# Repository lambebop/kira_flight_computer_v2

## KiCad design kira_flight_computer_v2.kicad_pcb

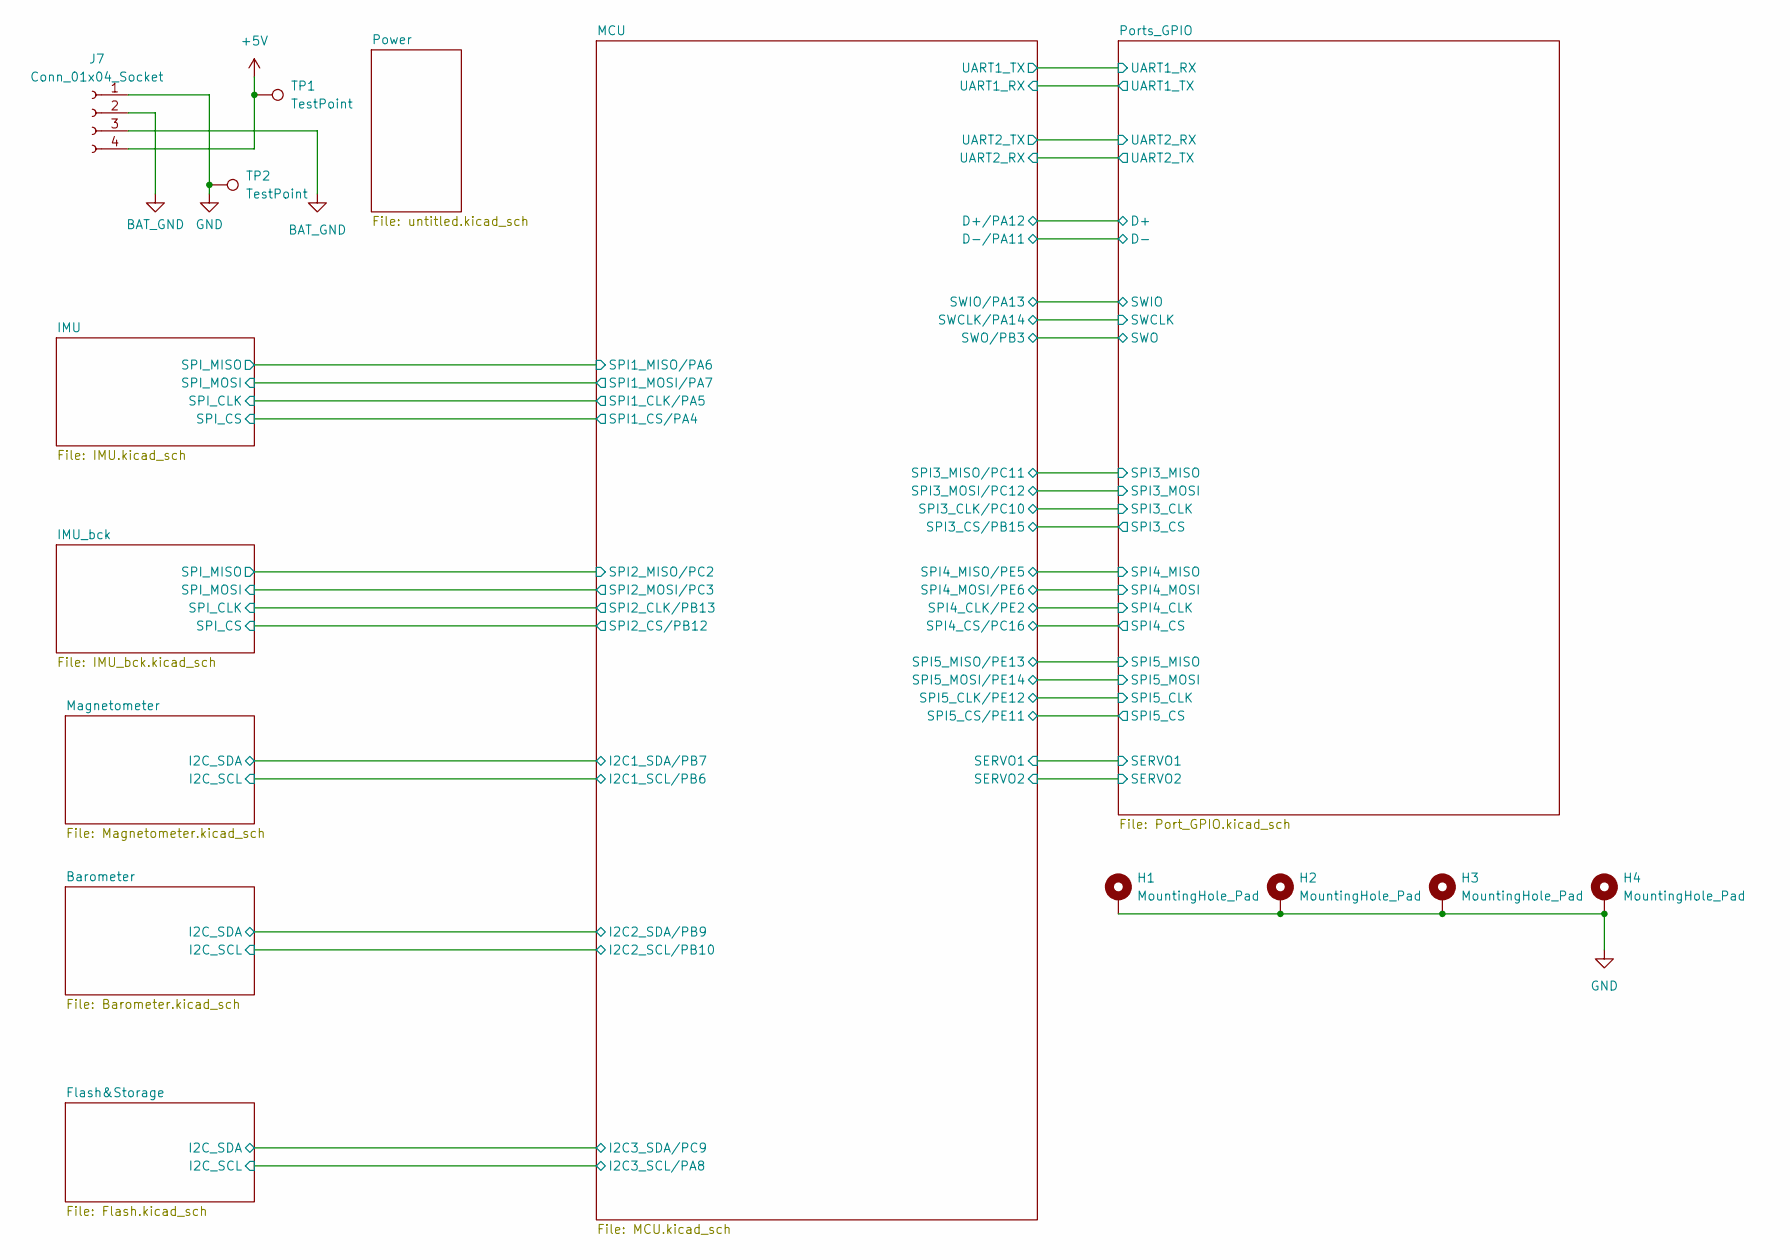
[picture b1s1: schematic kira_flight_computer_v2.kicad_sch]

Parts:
H1, H2, H3, H4: MountingHole_Pad; MountingHole_2.2mm_M2_Pad_TopBottom
J7: Conn_01x04_Socket; TerminalBlock_WAGO_2601-1104_1x04_P3.50mm_Horizontal
TP1, TP2: TestPoint; TestPoint_Pad_D1.0mm

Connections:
+5V: J7.4, TP1.1; also elsewhere on the board
BAT_GND: J7.2, J7.3
GND: H1.1, H2.1, H3.1, H4.1, J7.1, TP2.1; also elsewhere on the board

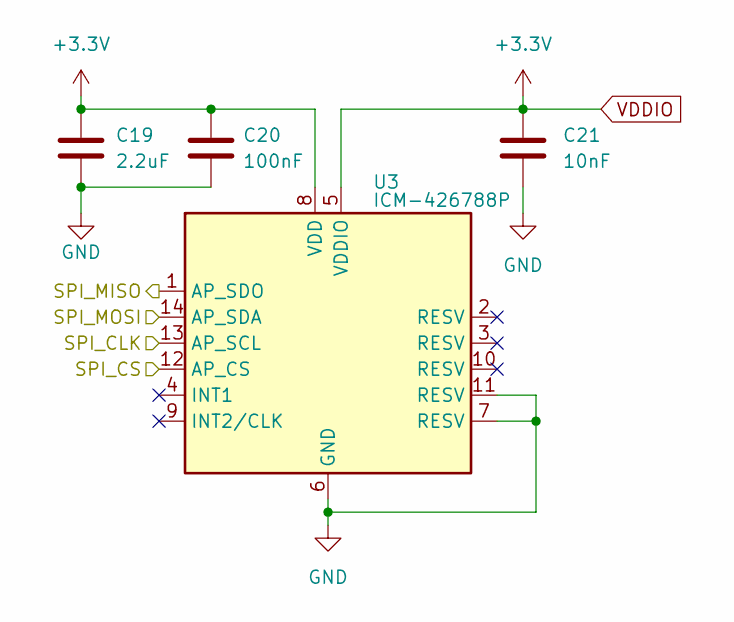
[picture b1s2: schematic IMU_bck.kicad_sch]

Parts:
C19: 2.2uF; C_0603_1608Metric_Pad1.08x0.95mm_HandSolder
C20: 100nF; C_0603_1608Metric_Pad1.08x0.95mm_HandSolder
C21: 10nF; C_0603_1608Metric_Pad1.08x0.95mm_HandSolder
U3: ICM-426788P; Bosch_LGA-14_3x2.5mm_P0.5mm

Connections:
/IMU_bck/SPI_CLK: U3.13 (AP_SCL); also elsewhere on the board
/IMU_bck/SPI_CS: U3.12 (AP_CS); also elsewhere on the board
/IMU_bck/SPI_MISO: U3.1 (AP_SDO); also elsewhere on the board
/IMU_bck/SPI_MOSI: U3.14 (AP_SDA); also elsewhere on the board
GND: C19.2, C20.2, C21.2, U3.6 (GND), U3.7 (RESV), U3.11 (RESV); also elsewhere on the board
VDDIO: C19.1, C20.1, C21.1, U3.5 (VDDIO), U3.8 (VDD); also elsewhere on the board

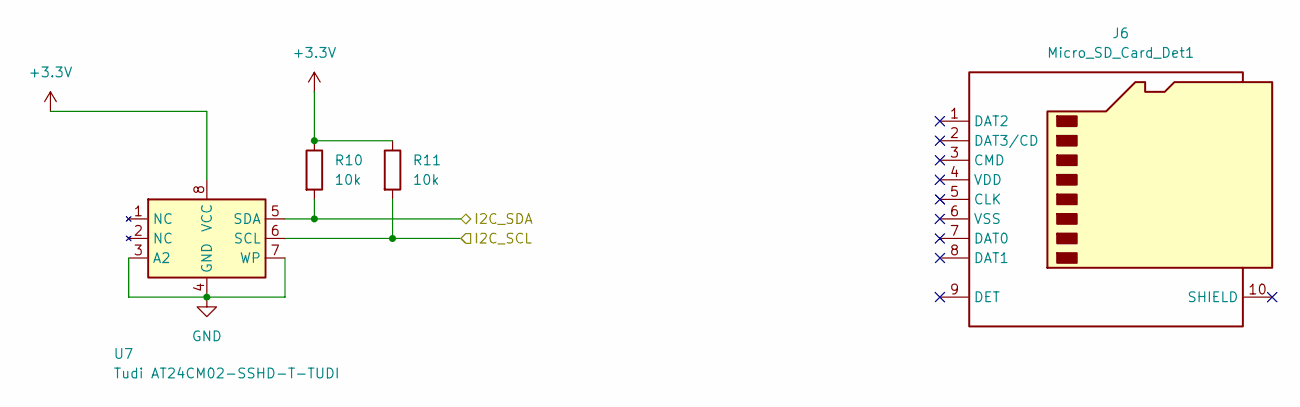
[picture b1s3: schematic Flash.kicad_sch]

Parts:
J6: Micro_SD_Card_Det1
R10, R11: 10k; R_0603_1608Metric
U7: Tudi AT24CM02-SSHD-T-TUDI; SOIC-8_3.9x4.9mm_P1.27mm

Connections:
/Flash&Storage/I2C_SCL: R11.2, U7.6 (SCL); also elsewhere on the board
/Flash&Storage/I2C_SDA: R10.2, U7.5 (SDA); also elsewhere on the board
GND: U7.3 (A2), U7.4 (GND), U7.7 (WP); also elsewhere on the board
VDDIO: R10.1, R11.1, U7.8 (VCC); also elsewhere on the board

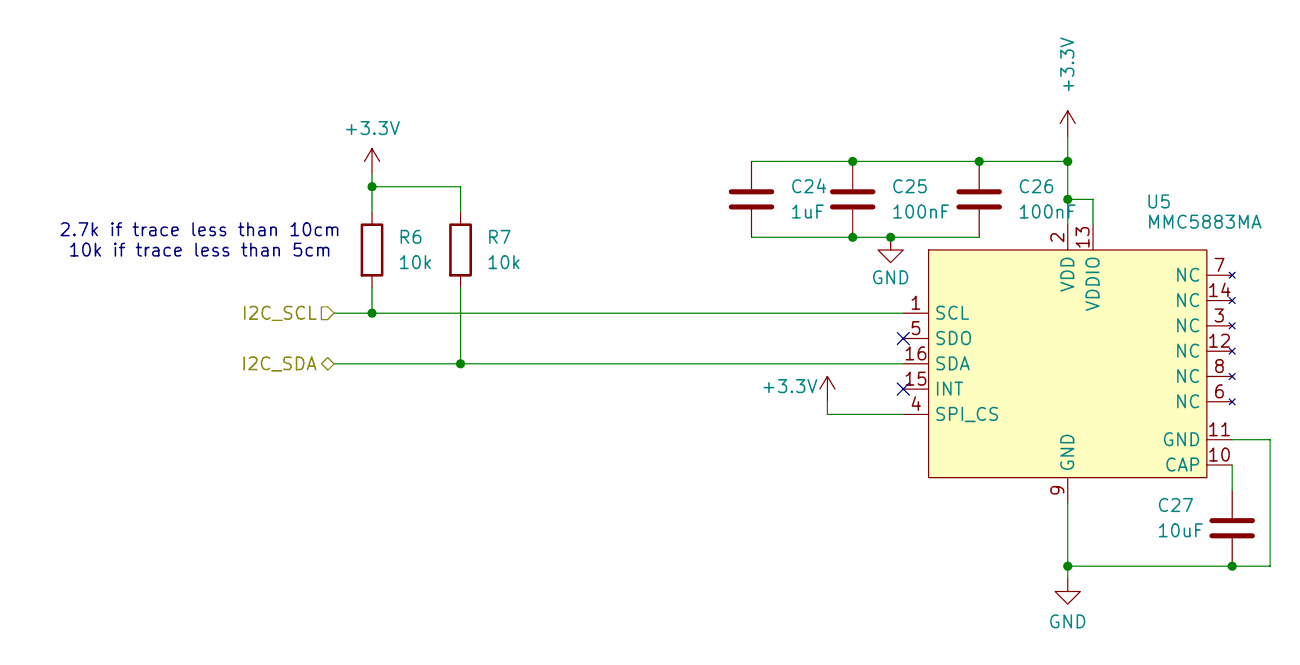
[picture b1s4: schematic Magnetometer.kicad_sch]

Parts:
C24: 1uF; C_0603_1608Metric_Pad1.08x0.95mm_HandSolder
C25, C26: 100nF; C_0603_1608Metric_Pad1.08x0.95mm_HandSolder
C27: 10uF; C_0603_1608Metric_Pad1.08x0.95mm_HandSolder
R6, R7: 10k; R_0603_1608Metric_Pad0.98x0.95mm_HandSolder
U5: MMC5883MA; LGA-16_3x3mm_P0.5mm

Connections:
/MCU/I2C1_SCL/PB6: R6.2, U5.1 (SCL); also elsewhere on the board
/MCU/I2C1_SDA/PB7: R7.2, U5.16 (SDA); also elsewhere on the board
GND: C24.2, C25.2, C26.2, C27.2, U5.9 (GND), U5.11 (GND); also elsewhere on the board
unnamed: C27.1, U5.10 (CAP)
VDDIO: C24.1, C25.1, C26.1, R6.1, R7.1, U5.2 (VDD), U5.4 (SPI_CS), U5.13 (VDDIO); also elsewhere on the board

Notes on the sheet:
2.7k if trace less than 10cm 10k if trace less than 5cm

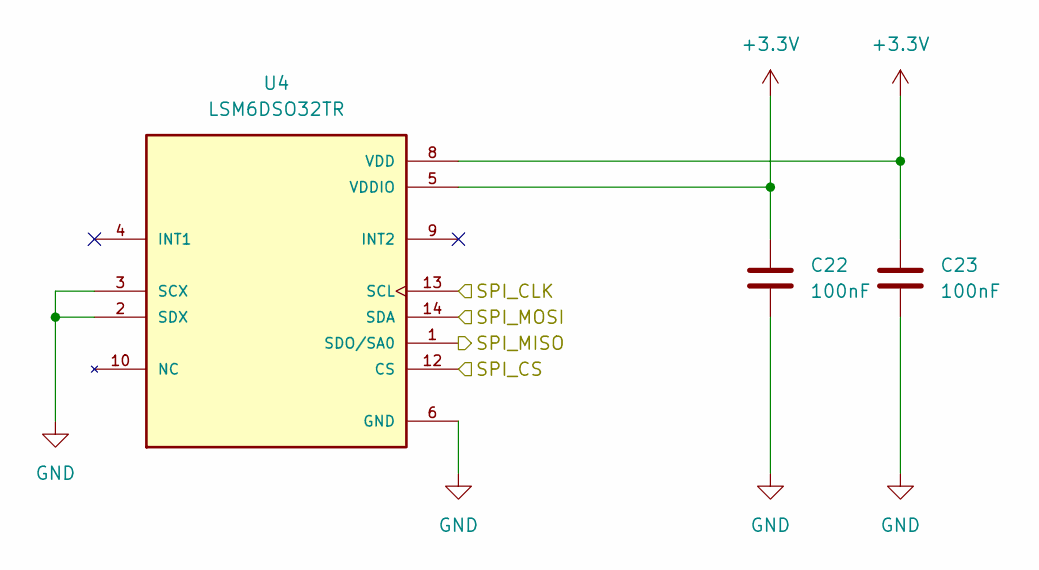
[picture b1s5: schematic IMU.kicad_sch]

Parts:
C22, C23: 100nF; C_0603_1608Metric_Pad1.08x0.95mm_HandSolder
U4: LSM6DSO32TR; XDCR_LSM6DSO32TR; PARTREV 1

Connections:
/IMU/SPI_CLK: U4.13 (SCL); also elsewhere on the board
/IMU/SPI_CS: U4.12 (CS); also elsewhere on the board
/IMU/SPI_MISO: U4.1 (SDO/SA0); also elsewhere on the board
/IMU/SPI_MOSI: U4.14 (SDA); also elsewhere on the board
GND: C22.2, C23.2, U4.2 (SDX), U4.3 (SCX), U4.6 (GND), U4.7 (GND); also elsewhere on the board
VDDIO: C22.1, C23.1, U4.5 (VDDIO), U4.8 (VDD); also elsewhere on the board

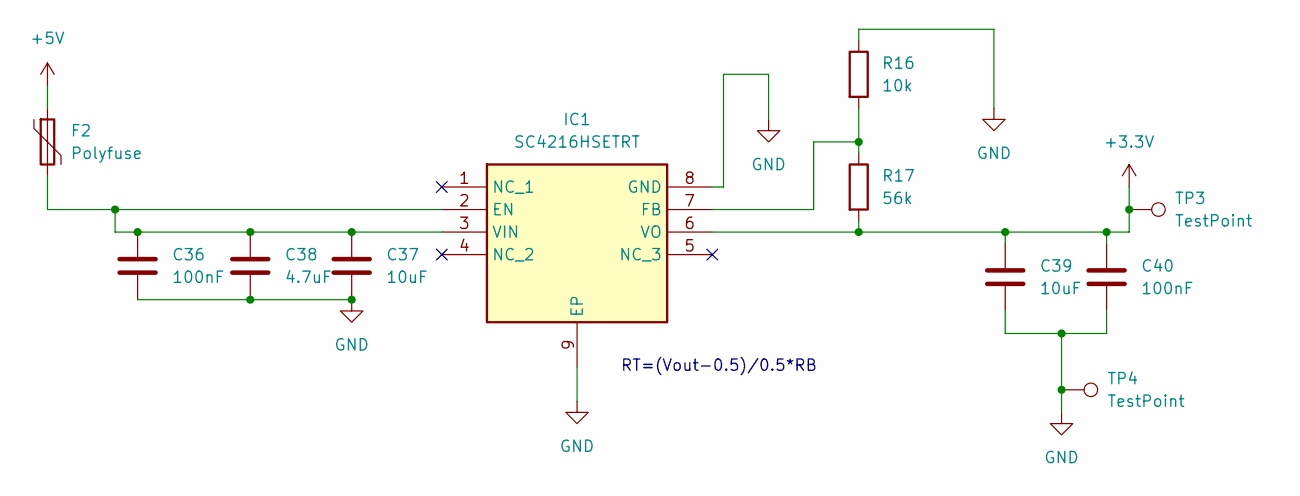
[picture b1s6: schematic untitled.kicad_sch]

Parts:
C36, C40: 100nF; C_0603_1608Metric
C37, C39: 10uF; C_1206_3216Metric
C38: 4.7uF; C_0603_1608Metric
F2: Polyfuse; Fuse_1206_3216Metric_Pad1.42x1.75mm_HandSolder
IC1: SC4216HSETRT; SOIC127P600X175-9N; Mouser Part Number 947-SC4216HSETRT
R16: 10k; R_0603_1608Metric
R17: 56k; R_0805_2012Metric
TP3, TP4: TestPoint; TestPoint_Pad_D1.0mm

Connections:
+5V: F2.1; also elsewhere on the board
GND: C36.2, C37.2, C38.2, C39.2, C40.2, IC1.8 (GND), IC1.9 (EP), R16.1, TP4.1; also elsewhere on the board
unnamed: C36.1, C37.1, C38.1, F2.2, IC1.2 (EN), IC1.3 (VIN)
unnamed: IC1.7 (FB), R16.2, R17.1
VDDIO: C39.1, C40.1, IC1.6 (VO), R17.2, TP3.1; also elsewhere on the board

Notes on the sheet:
RT=(Vout-0.5)/0.5*RB

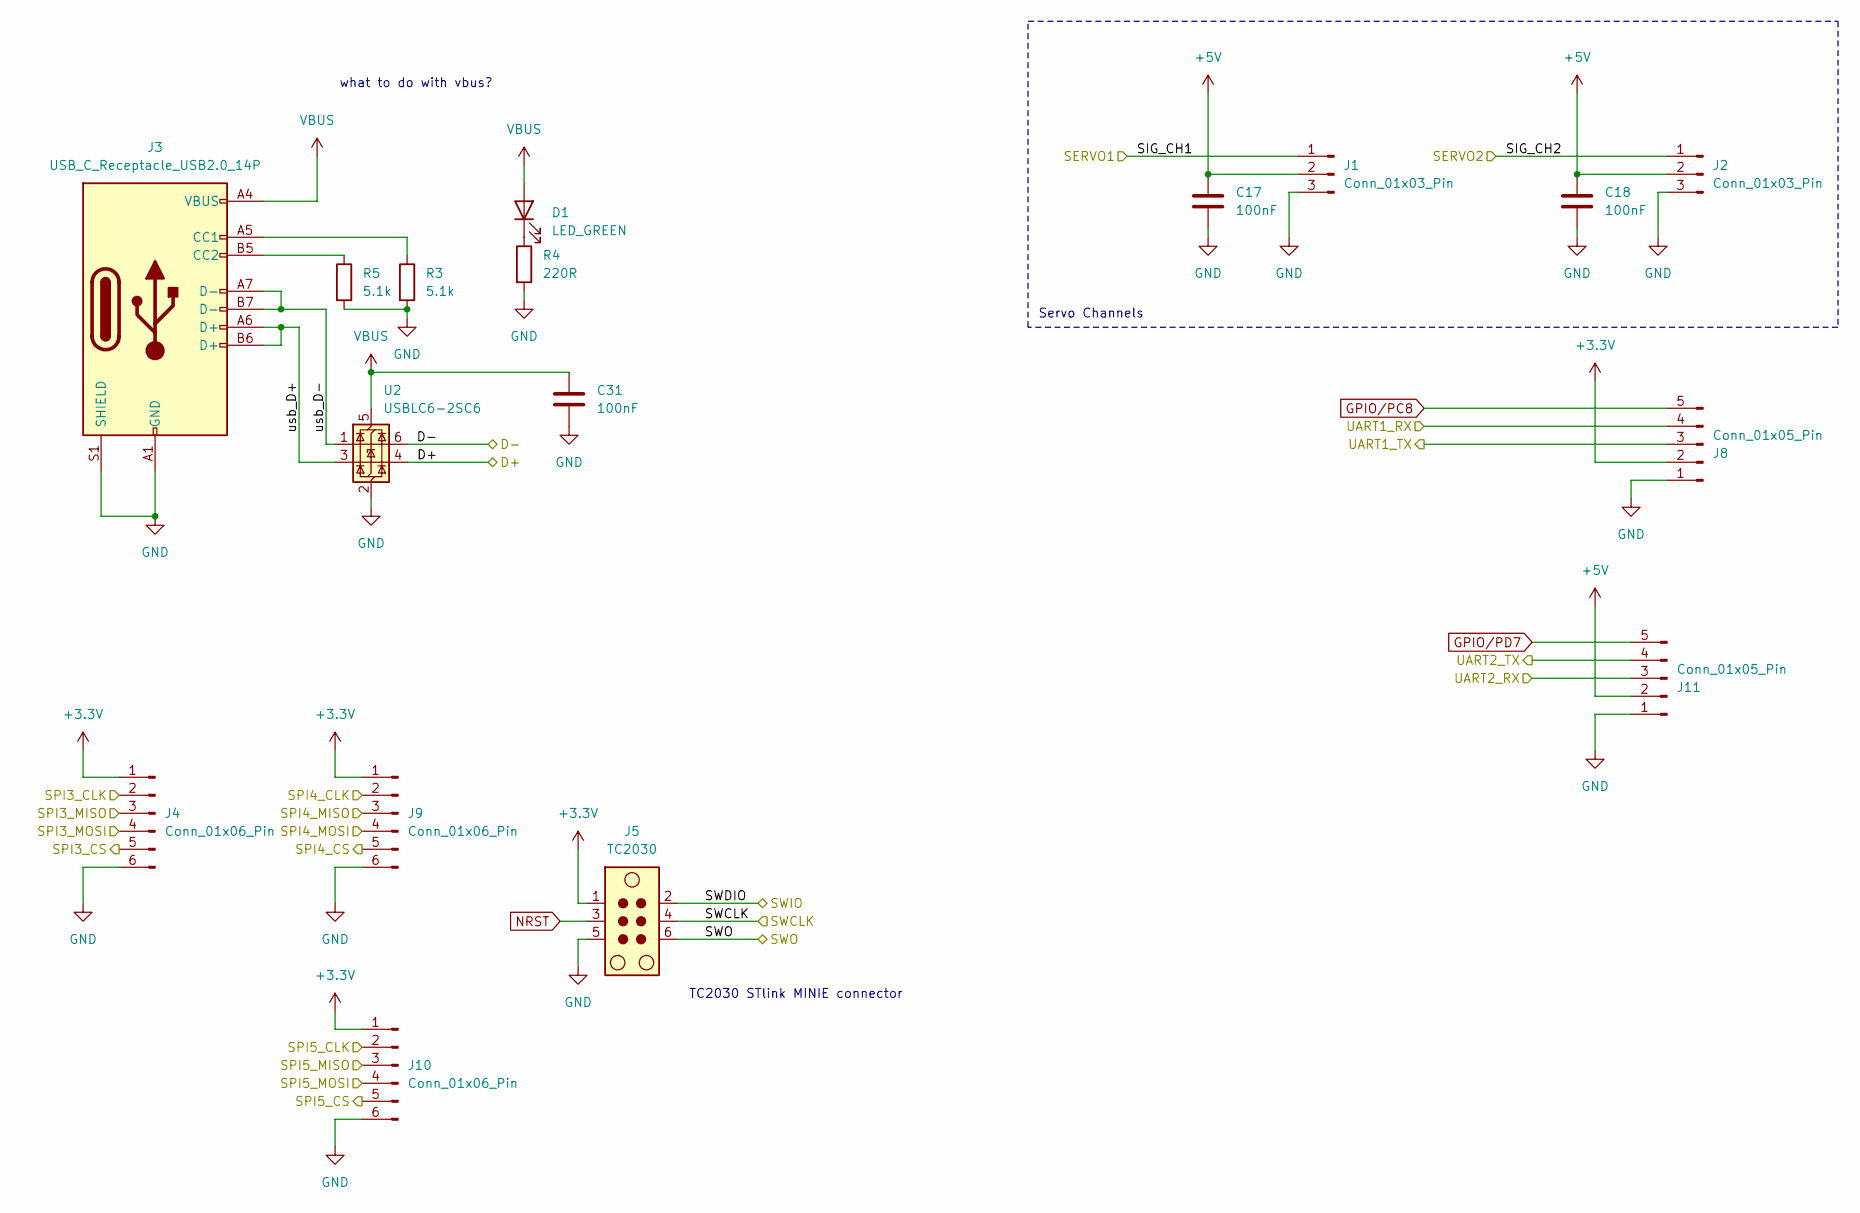
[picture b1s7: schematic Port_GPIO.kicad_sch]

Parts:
C17, C18, C31: 100nF; C_0603_1608Metric_Pad1.08x0.95mm_HandSolder
D1: LED_GREEN; LED_0603_1608Metric
J1, J2: Conn_01x03_Pin; JST_XH_S3B-XH-A_1x03_P2.50mm_Horizontal
J3: USB_C_Receptacle_USB2.0_14P; USB_C_Receptacle_GCT_USB4105-xx-A_16P_TopMnt_Horizontal
J4, J9, J10: Conn_01x06_Pin; JST_GH_BM06B-GHS-TBT_1x06-1MP_P1.25mm_Vertical
J5: TC2030; Tag-Connect_TC2030-IDC-NL_2x03_P1.27mm_Vertical
J8, J11: Conn_01x05_Pin; JST_GH_BM05B-GHS-TBT_1x05-1MP_P1.25mm_Vertical
R3, R5: 5.1k; R_0603_1608Metric_Pad0.98x0.95mm_HandSolder
R4: 220R; R_0603_1608Metric_Pad0.98x0.95mm_HandSolder
U2: USBLC6-2SC6; SOT-23-6

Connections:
+5V: C17.1, C18.1, J1.2, J2.2, J11.2; also elsewhere on the board
/MCU/SPI3_CLK/PC10: J4.2; also elsewhere on the board
/MCU/SPI3_CS/PB15: J4.5; also elsewhere on the board
/MCU/SPI3_MISO/PC11: J4.3; also elsewhere on the board
/MCU/SPI3_MOSI/PC12: J4.4; also elsewhere on the board
/MCU/SPI4_CLK/PE2: J9.2; also elsewhere on the board
/MCU/SPI4_CS/PC16: J9.5; also elsewhere on the board
/MCU/SPI4_MISO/PE5: J9.3; also elsewhere on the board
/MCU/SPI4_MOSI/PE6: J9.4; also elsewhere on the board
/MCU/SPI5_CLK/PE12: J10.2; also elsewhere on the board
/MCU/SPI5_CS/PE11: J10.5; also elsewhere on the board
/MCU/SPI5_MISO/PE13: J10.3; also elsewhere on the board
/MCU/SPI5_MOSI/PE14: J10.4; also elsewhere on the board
/MCU/UART1_RX: J8.3; also elsewhere on the board
/MCU/UART1_TX: J8.4; also elsewhere on the board
/MCU/UART2_RX: J11.4; also elsewhere on the board
/MCU/UART2_TX: J11.3; also elsewhere on the board
/Ports_GPIO/D+: U2.4 (I/O2); also elsewhere on the board
/Ports_GPIO/D-: U2.6 (I/O1); also elsewhere on the board
/Ports_GPIO/SIG_CH1: J1.1; also elsewhere on the board
/Ports_GPIO/SIG_CH2: J2.1; also elsewhere on the board
/Ports_GPIO/SWCLK: J5.4; also elsewhere on the board
/Ports_GPIO/SWDIO: J5.2; also elsewhere on the board
/Ports_GPIO/SWO: J5.6; also elsewhere on the board
/Ports_GPIO/usb_D+: J3.A6 (D+), J3.B6 (D+), U2.3 (I/O2)
/Ports_GPIO/usb_D-: J3.A7 (D-), J3.B7 (D-), U2.1 (I/O1)
GND: C17.2, C18.2, C31.2, J1.3, J2.3, J3.A1 (GND), J3.A12 (GND), J3.B1 (GND), J3.B12 (GND), J3.S1 (SHIELD), J4.6, J5.5, J8.1, J9.6, J10.6, J11.1, R3.2, R4.2, R5.2, U2.2 (GND); also elsewhere on the board
GPIO/PC8: J8.5; also elsewhere on the board
GPIO/PD7: J11.5; also elsewhere on the board
NRST: J5.3; also elsewhere on the board
unnamed: D1.1 (K), R4.1
unnamed: J3.A5 (CC1), R3.1
unnamed: J3.B5 (CC2), R5.1
VBUS: C31.1, D1.2 (A), J3.A4 (VBUS), J3.A9 (VBUS), J3.B4 (VBUS), J3.B9 (VBUS), U2.5 (VBUS)
VDDIO: J4.1, J5.1, J8.2, J9.1, J10.1; also elsewhere on the board

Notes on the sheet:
what to do with vbus?
TC2030 STlink MINIE connector
Servo Channels

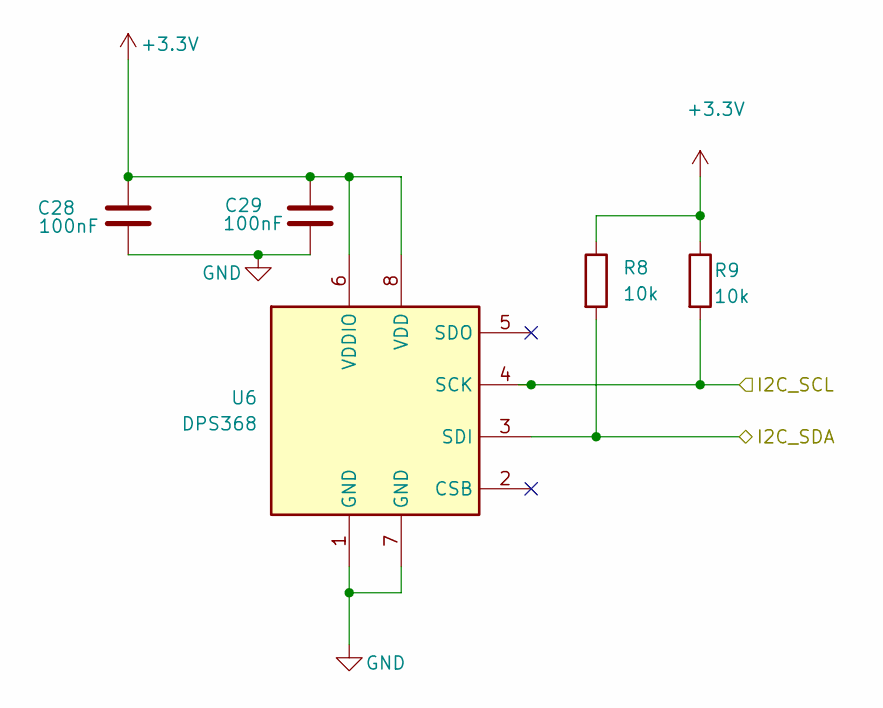
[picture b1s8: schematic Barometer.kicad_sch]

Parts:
C28, C29: 100nF; C_0603_1608Metric_Pad1.08x0.95mm_HandSolder
R8, R9: 10k; R_0603_1608Metric
U6: DPS368; Bosch_LGA-8_2x2.5mm_P0.65mm_ClockwisePinNumbering

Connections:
/Barometer/I2C_SCL: R9.2, U6.4 (SCK); also elsewhere on the board
/Barometer/I2C_SDA: R8.2, U6.3 (SDI); also elsewhere on the board
GND: C28.2, C29.2, U6.1 (GND), U6.7 (GND); also elsewhere on the board
VDDIO: C28.1, C29.1, R8.1, R9.1, U6.6 (VDDIO), U6.8 (VDD); also elsewhere on the board

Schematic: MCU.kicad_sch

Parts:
C1, C2, C30: 100nF; C_0603_1608Metric
C3, C4, C5, C6, C7, C9, C12, C14: 100nF; C_0603_1608Metric_Pad1.08x0.95mm_HandSolder
C8: 4.7uF; C_0603_1608Metric
C10, C13: 1uF; C_0603_1608Metric_Pad1.08x0.95mm_HandSolder
C11, C15, C16: 4.7uF; C_0603_1608Metric_Pad1.08x0.95mm_HandSolder
FB1: 120R; L_1206_3216Metric
R1, R2: 10k; R_0603_1608Metric
SW1: SW_SPST; SW_SPST_B3U-1000P-B
U1: STM32F411VETx; LQFP-100_14x14mm_P0.5mm
U8: USBLC6-2SC6; SOT-23-6
Y1: Resonator; Crystal_SMD_SeikoEpson_TSX3225-4Pin_3.2x2.5mm

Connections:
+5V: C30.1, U8.5 (VBUS); also elsewhere on the board
/Barometer/I2C_SCL: U1.47 (PB10); also elsewhere on the board
/Barometer/I2C_SDA: U1.96 (PB9); also elsewhere on the board
/Flash&Storage/I2C_SCL: U1.67 (PA8); also elsewhere on the board
/Flash&Storage/I2C_SDA: U1.66 (PC9); also elsewhere on the board
/IMU/SPI_CLK: U1.30 (PA5); also elsewhere on the board
/IMU/SPI_CS: U1.29 (PA4); also elsewhere on the board
/IMU/SPI_MISO: U1.31 (PA6); also elsewhere on the board
/IMU/SPI_MOSI: U1.32 (PA7); also elsewhere on the board
/IMU_bck/SPI_CLK: U1.52 (PB13); also elsewhere on the board
/IMU_bck/SPI_CS: U1.51 (PB12); also elsewhere on the board
/IMU_bck/SPI_MISO: U1.17 (PC2); also elsewhere on the board
/IMU_bck/SPI_MOSI: U1.18 (PC3); also elsewhere on the board
/MCU/I2C1_SCL/PB6: U1.92 (PB6); also elsewhere on the board
/MCU/I2C1_SDA/PB7: U1.93 (PB7); also elsewhere on the board
/MCU/SPI3_CLK/PC10: U1.78 (PC10); also elsewhere on the board
/MCU/SPI3_CS/PB15: U1.54 (PB15); also elsewhere on the board
/MCU/SPI3_MISO/PC11: U1.79 (PC11); also elsewhere on the board
/MCU/SPI3_MOSI/PC12: U1.80 (PC12); also elsewhere on the board
/MCU/SPI4_CLK/PE2: U1.1 (PE2); also elsewhere on the board
/MCU/SPI4_CS/PC16: U1.16 (PC1); also elsewhere on the board
/MCU/SPI4_MISO/PE5: U1.4 (PE5); also elsewhere on the board
/MCU/SPI4_MOSI/PE6: U1.5 (PE6); also elsewhere on the board
/MCU/SPI5_CLK/PE12: U1.43 (PE12); also elsewhere on the board
/MCU/SPI5_CS/PE11: U1.42 (PE11); also elsewhere on the board
/MCU/SPI5_MISO/PE13: U1.44 (PE13); also elsewhere on the board
/MCU/SPI5_MOSI/PE14: U1.45 (PE14); also elsewhere on the board
/MCU/UART1_RX: U1.69 (PA10); also elsewhere on the board
/MCU/UART1_TX: U1.68 (PA9); also elsewhere on the board
/MCU/UART2_RX: U1.87 (PD6); also elsewhere on the board
/MCU/UART2_TX: U1.86 (PD5); also elsewhere on the board
/Ports_GPIO/D+: U1.71 (PA12); also elsewhere on the board
/Ports_GPIO/D-: U1.70 (PA11); also elsewhere on the board
/Ports_GPIO/SIG_CH1: U8.4 (I/O2); also elsewhere on the board
/Ports_GPIO/SIG_CH2: U8.6 (I/O1); also elsewhere on the board
/Ports_GPIO/SWCLK: U1.76 (PA14); also elsewhere on the board
/Ports_GPIO/SWDIO: U1.72 (PA13); also elsewhere on the board
/Ports_GPIO/SWO: U1.89 (PB3); also elsewhere on the board
GND: C1.2, C2.2, C3.2, C4.2, C5.2, C6.2, C7.2, C8.2, C9.2, C10.2, C11.2, C12.2, C13.2, C14.2, C15.2, C16.2, C30.2, R2.1, U1.10 (VSS), U1.20 (VSSA), U1.27 (VSS), U1.49 (VSS), U1.74 (VSS), U1.99 (VSS), U8.2 (GND), Y1.2; also elsewhere on the board
GPIO/PC8: U1.65 (PC8); also elsewhere on the board
GPIO/PD7: U1.88 (PD7); also elsewhere on the board
NRST: C14.1, R1.1, U1.14 (NRST); also elsewhere on the board
unnamed: R2.2, SW1.2 (B), U1.94 (BOOT0)
unnamed: U1.90 (PB4), U8.3 (I/O2)
unnamed: U1.91 (PB5), U8.1 (I/O1)
unnamed: U1.12 (PH0), Y1.1
unnamed: U1.13 (PH1), Y1.3
unnamed: C15.1, U1.48 (VCAP1)
unnamed: C16.1, U1.73 (VCAP2)
VDDIO: C1.1, C2.1, C3.1, C4.1, C5.1, C6.1, C7.1, C8.1, C11.1, FB1.2, R1.2, SW1.1 (A), U1.6 (VBAT), U1.11 (VDD), U1.19 (VDD), U1.28 (VDD), U1.50 (VDD), U1.75 (VDD), U1.100 (VDD); also elsewhere on the board
VREF+: C9.1, C10.1, C12.1, C13.1, FB1.1, U1.21 (VREF+), U1.22 (VDDA)

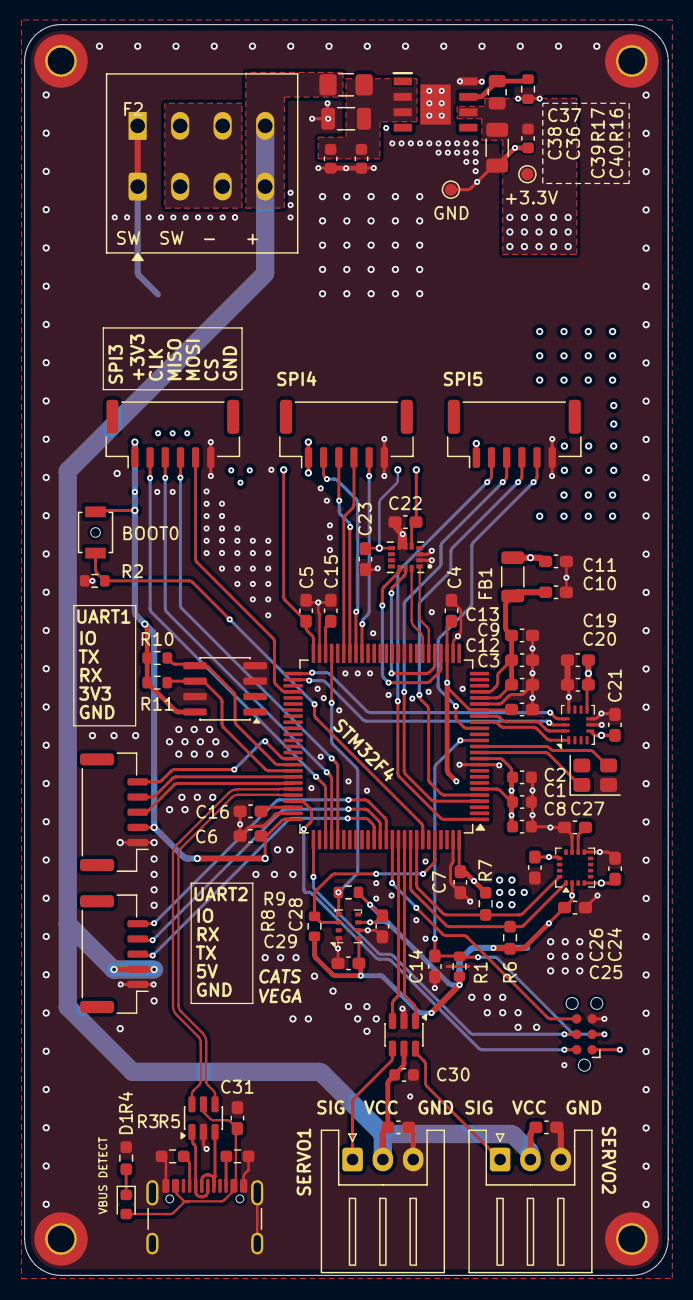
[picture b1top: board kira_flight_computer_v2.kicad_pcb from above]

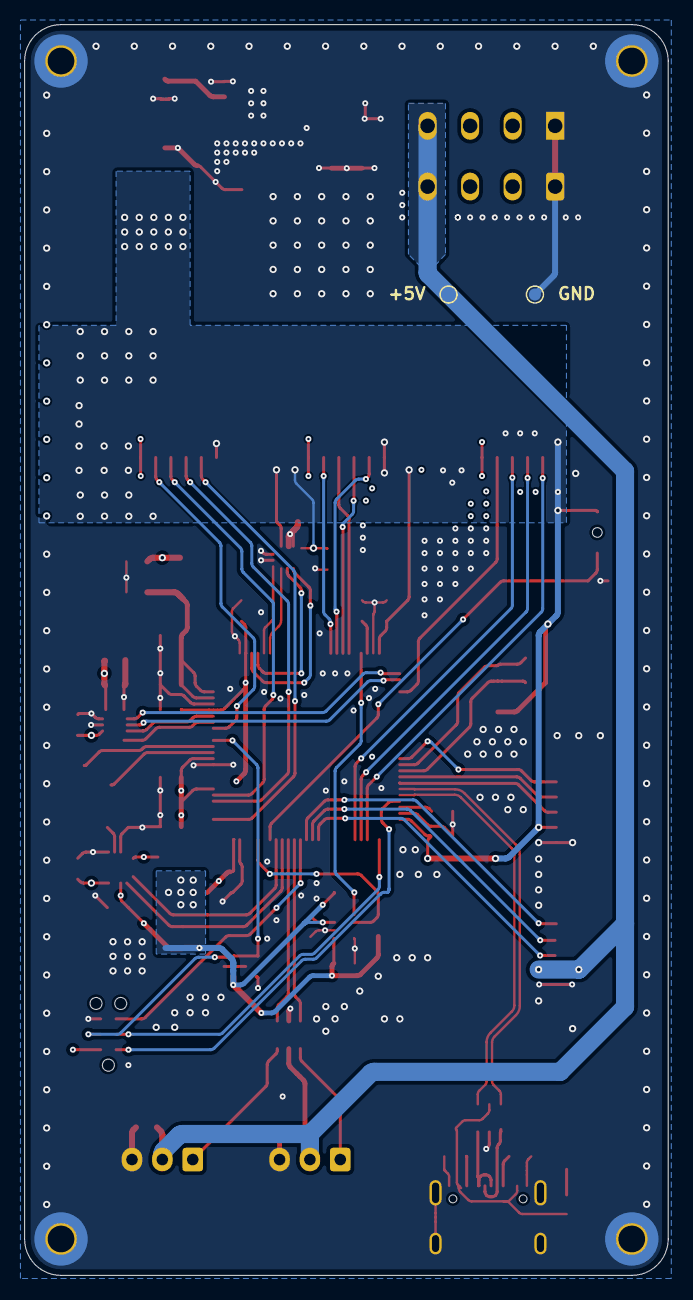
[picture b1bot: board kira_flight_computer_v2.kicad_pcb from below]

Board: 4 copper layers, 53.0 x 103.0 mm, 81 parts (2 on the bottom side), 61 nets.

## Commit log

2026-05-11 Add via stitching
2026-05-13 Add Borderr
2026-05-14 Updatte
2026-05-18 update step file
